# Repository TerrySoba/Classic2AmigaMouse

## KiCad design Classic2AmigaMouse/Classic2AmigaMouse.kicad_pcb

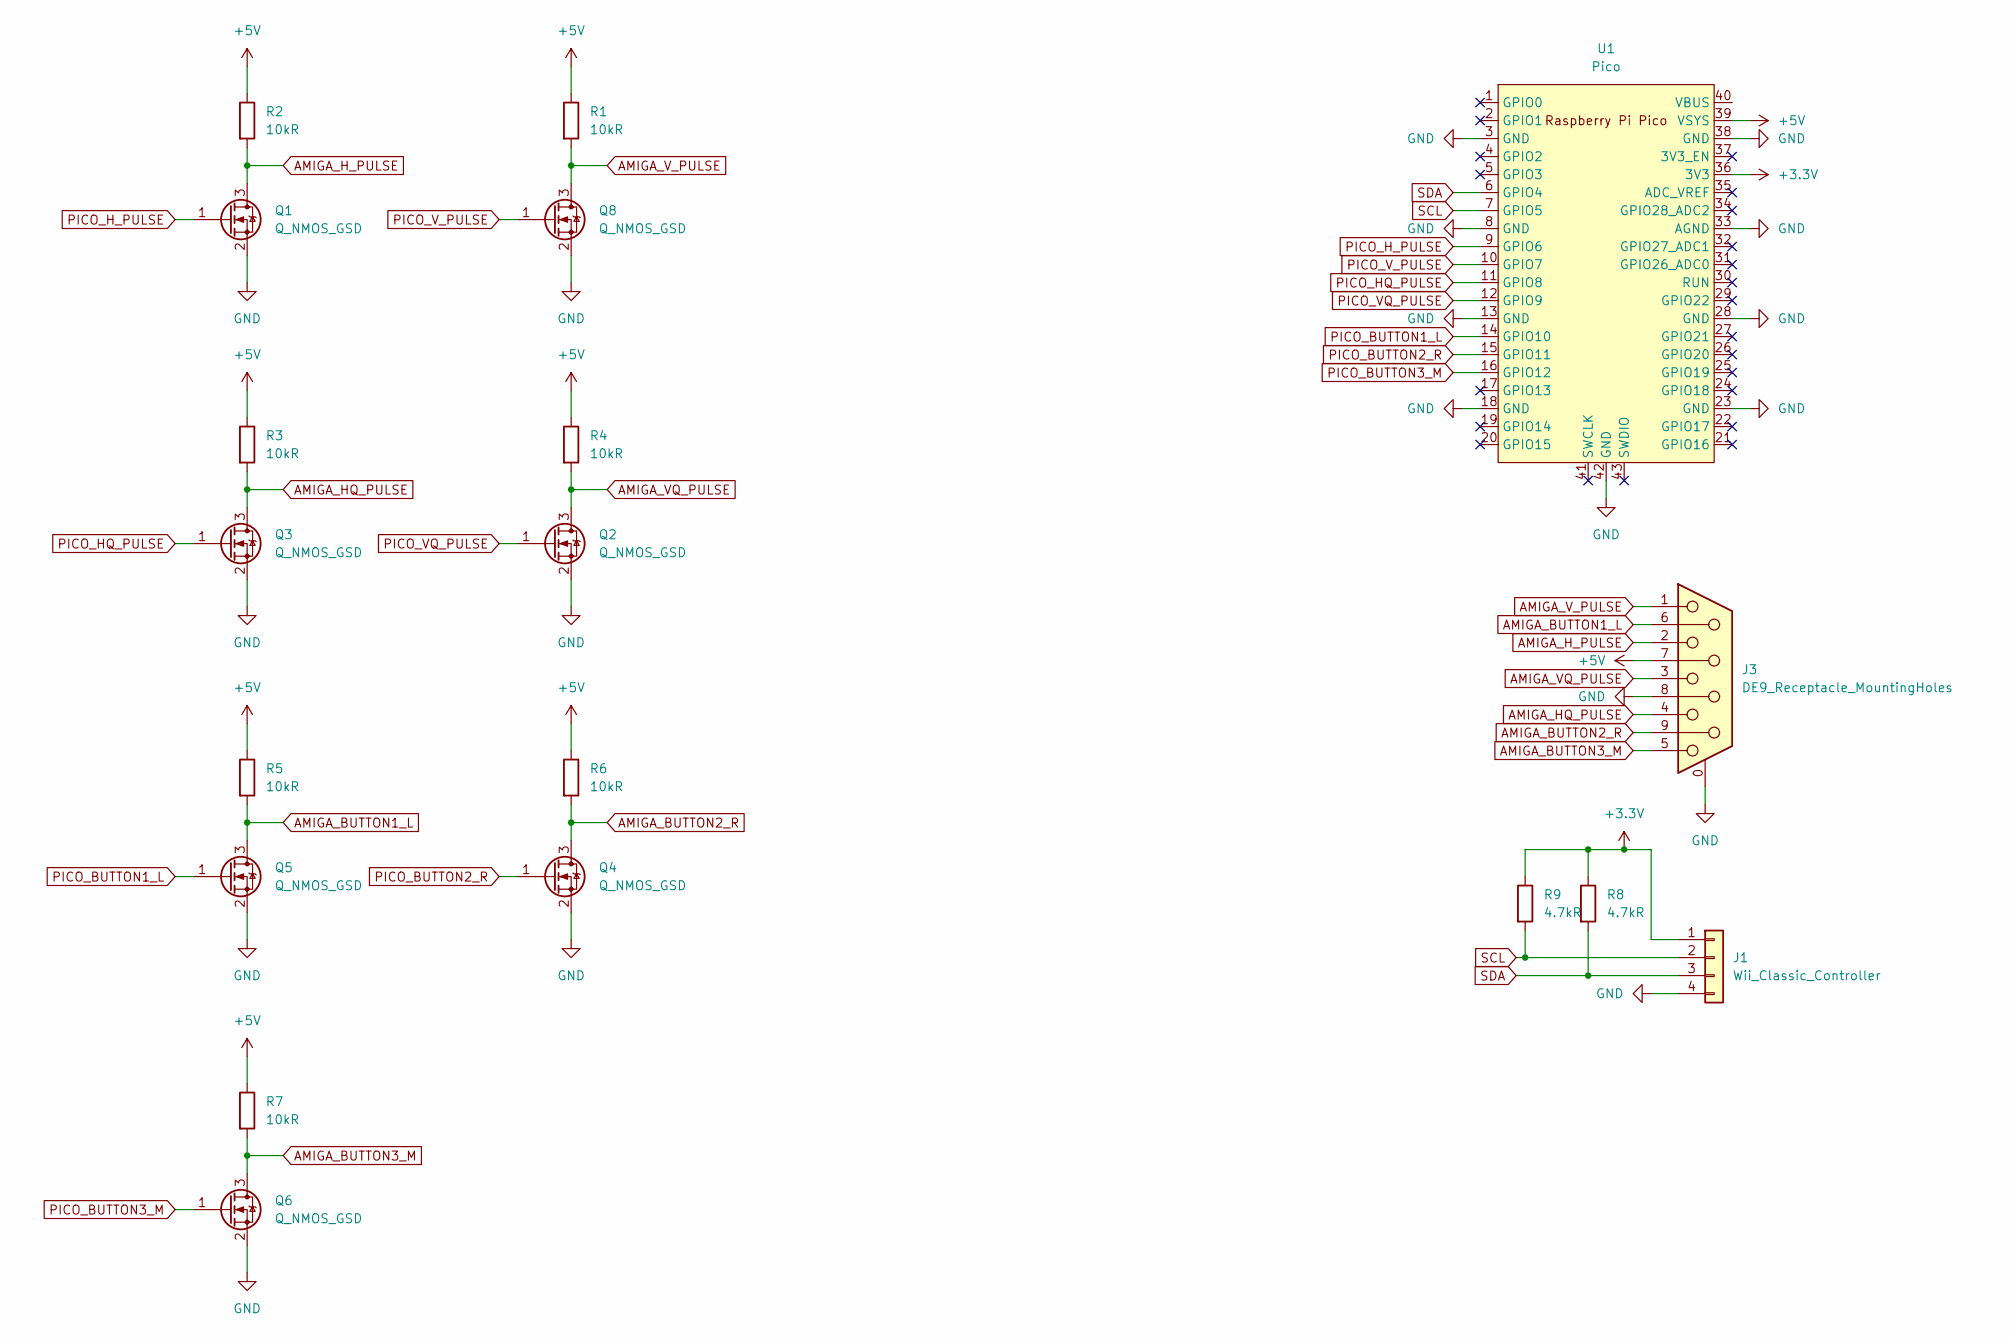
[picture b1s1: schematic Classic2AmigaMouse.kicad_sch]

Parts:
J1: Wii_Classic_Controller; Molex_KK-254_AE-6410-04A_1x04_P2.54mm_Vertical
J3: DE9_Receptacle_MountingHoles; DSUB-9_Female_Horizontal_P2.77x2.84mm_EdgePinOffset7.70mm_H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
Q1, Q2, Q3, Q4, Q5, Q6, Q8: Q_NMOS_GSD; SOT-23_Handsoldering
R1, R2, R3, R4, R5, R6, R7: 10kR; R_0805_2012Metric_Pad1.20x1.40mm_HandSolder
R8, R9: 4.7kR; R_0805_2012Metric_Pad1.20x1.40mm_HandSolder
U1: Pico; RPi_Pico_SMD_TH

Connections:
+3.3V: J1.1, R8.1, R9.1, U1.36 (3V3)
+5V: J3.7, R1.1, R2.1, R3.1, R4.1, R5.1, R6.1, R7.1, U1.39 (VSYS)
AMIGA_BUTTON1_L: J3.6, Q5.3 (D), R5.2
AMIGA_BUTTON2_R: J3.9, Q4.3 (D), R6.2
AMIGA_BUTTON3_M: J3.5, Q6.3 (D), R7.2
AMIGA_HQ_PULSE: J3.4, Q3.3 (D), R3.2
AMIGA_H_PULSE: J3.2, Q1.3 (D), R2.2
AMIGA_VQ_PULSE: J3.3, Q2.3 (D), R4.2
AMIGA_V_PULSE: J3.1, Q8.3 (D), R1.2
GND: J1.4, J3.0 (PAD), J3.8, Q1.2 (S), Q2.2 (S), Q3.2 (S), Q4.2 (S), Q5.2 (S), Q6.2 (S), Q8.2 (S), U1.3 (GND), U1.8 (GND), U1.13 (GND), U1.18 (GND), U1.23 (GND), U1.28 (GND), U1.33 (AGND), U1.38 (GND), U1.42 (GND)
PICO_BUTTON1_L: Q5.1 (G), U1.14 (GPIO10)
PICO_BUTTON2_R: Q4.1 (G), U1.15 (GPIO11)
PICO_BUTTON3_M: Q6.1 (G), U1.16 (GPIO12)
PICO_HQ_PULSE: Q3.1 (G), U1.11 (GPIO8)
PICO_H_PULSE: Q1.1 (G), U1.9 (GPIO6)
PICO_VQ_PULSE: Q2.1 (G), U1.12 (GPIO9)
PICO_V_PULSE: Q8.1 (G), U1.10 (GPIO7)
SCL: J1.2, R9.2, U1.7 (GPIO5)
SDA: J1.3, R8.2, U1.6 (GPIO4)

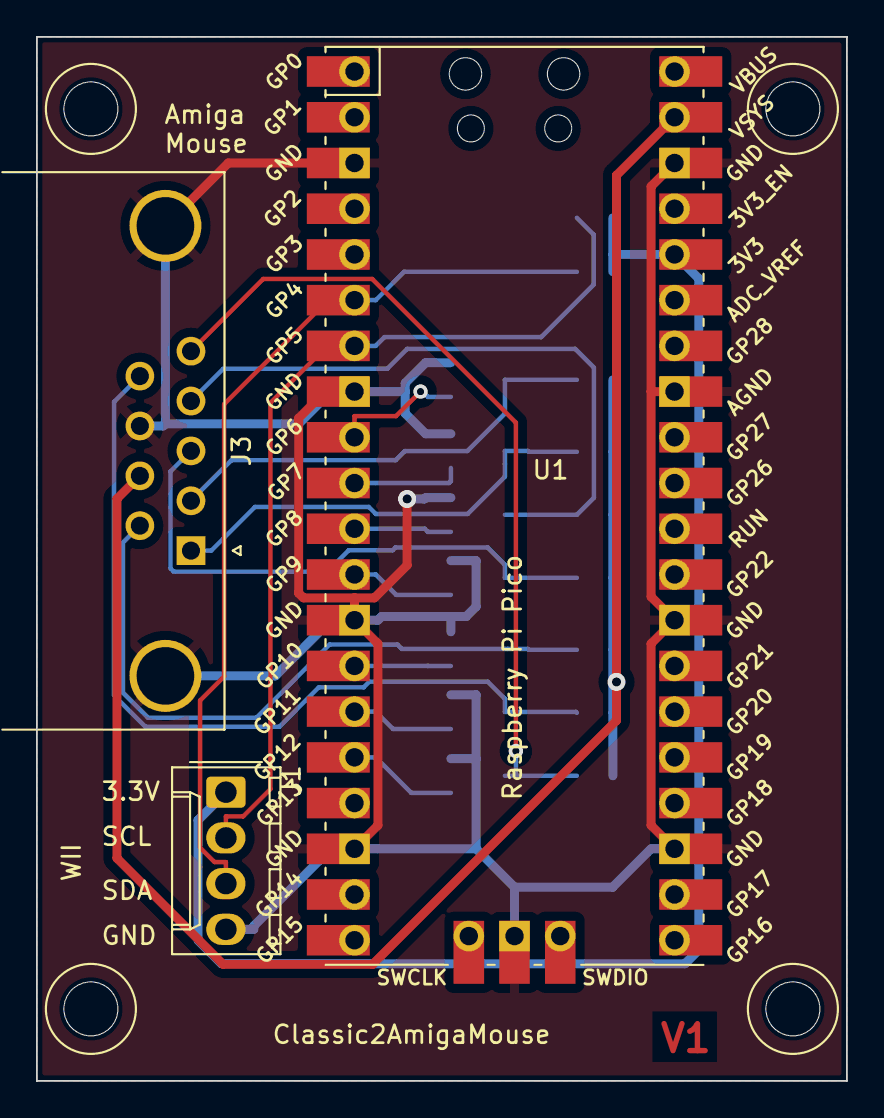
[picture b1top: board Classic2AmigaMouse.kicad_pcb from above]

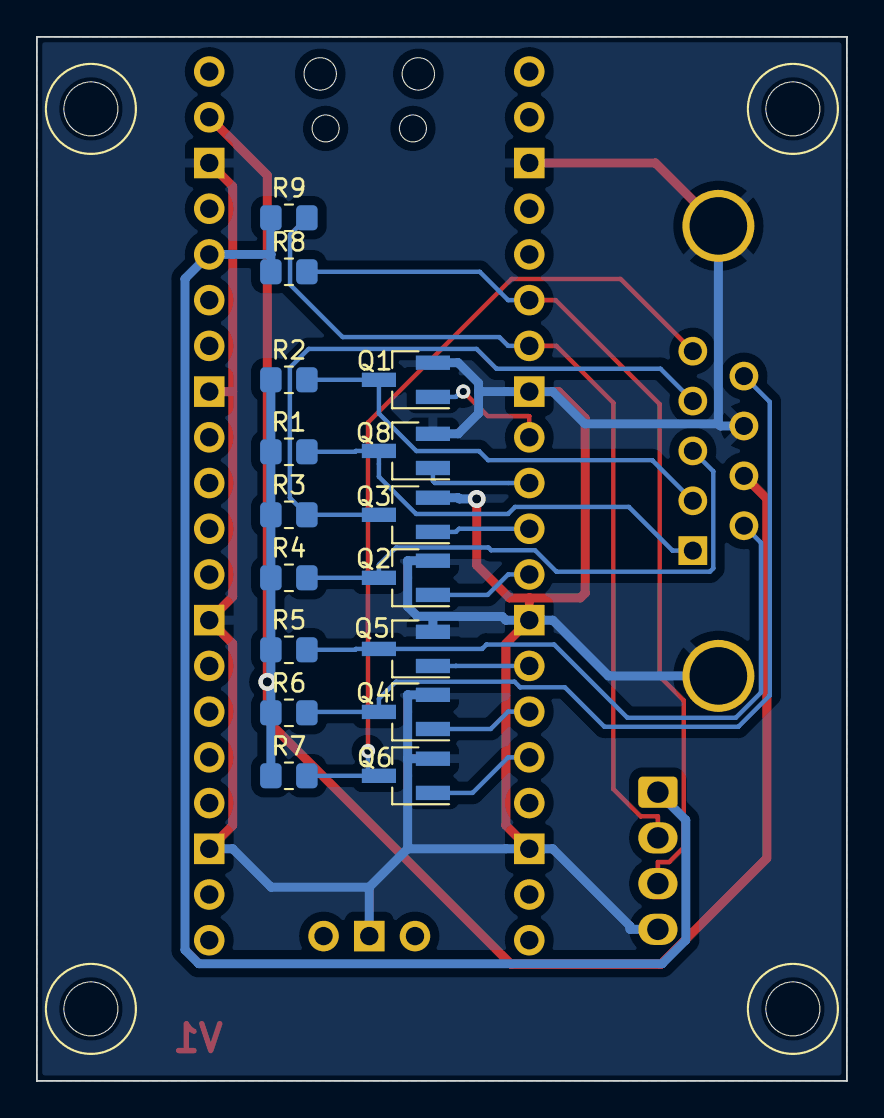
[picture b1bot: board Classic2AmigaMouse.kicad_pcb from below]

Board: 2 copper layers, 45.0 x 58.0 mm, 19 parts (16 on the bottom side), 19 nets.

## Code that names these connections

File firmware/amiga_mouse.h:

#ifndef AMIGA_MOUSE_H_
#define AMIGA_MOUSE_H_

#include <stdbool.h>
#include <stdint.h>

typedef enum
{
    AXIS_VERTICAL,
    AXIS_HORIZONTAL,
} MouseAxis;

// This enum defines what the GPIO pins are used for on the Amiga side
typedef enum
{
    AMIGA_H_PULSE = 6,
    AMIGA_V_PULSE = 7,
    AMIGA_HQ_PULSE = 8,
    AMIGA_VQ_PULSE = 9,
    AMIGA_LEFT_BUTTON = 10,
    AMIGA_RIGHT_BUTTON = 11,
    AMIGA_MIDDLE_BUTTON = 12,
} AmigaOutputGPIO;

#define AMIGA_JOYSTICK_BUTTON AMIGA_LEFT_BUTTON
#define AMIGA_JOYSTICK_LEFT   AMIGA_VQ_PULSE
#define AMIGA_JOYSTICK_RIGHT  AMIGA_HQ_PULSE
#define AMIGA_JOYSTICK_UP     AMIGA_V_PULSE
#define AMIGA_JOYSTICK_DOWN   AMIGA_H_PULSE

void initializeAmigaOutputGPIO();
void setAmigaOutput(AmigaOutputGPIO output, bool value);
void advanceAxisState(MouseAxis axis, uint32_t* state, int32_t direction);


#endif

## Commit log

2023-12-28 Initial Import
2023-12-29 Add initial firmware setup
2023-12-29 Add first somewhat working code
2023-12-29 Add error handling
2023-12-29 First maybe working implementation for mouse
2023-12-30 Also read analog stick
2023-12-30 Allow usage of analog stick for mouse
2024-01-03 Update mouse speed mapping and I2C polling frequency
2024-01-05 Change button mapping; Fix analog mouse
2024-01-06 Update BOM
2024-01-10 Add joystick support
